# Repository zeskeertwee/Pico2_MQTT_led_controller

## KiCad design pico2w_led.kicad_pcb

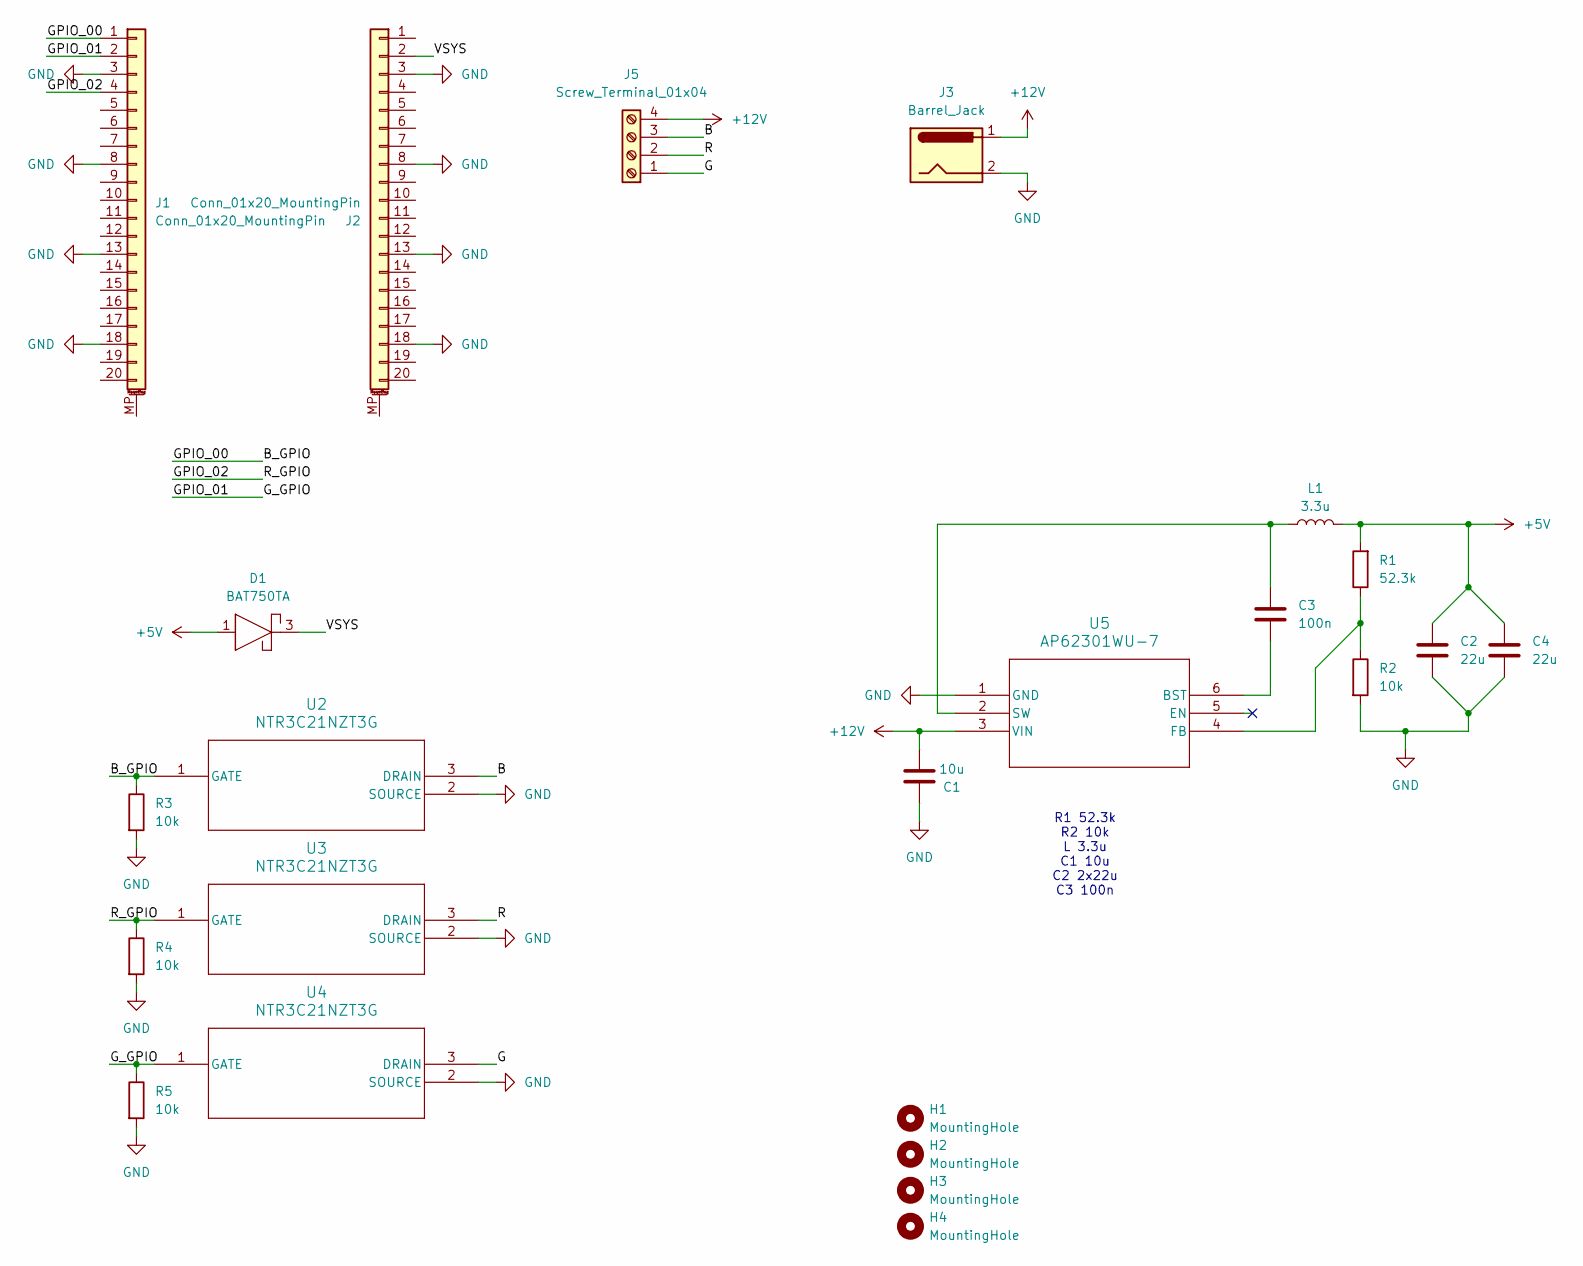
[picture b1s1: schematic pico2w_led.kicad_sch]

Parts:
C1: 10u; C_0805_2012Metric
C2, C4: 22u; C_1206_3216Metric
C3: 100n; C_0805_2012Metric
D1: BAT750TA; TSOT-23
H1, H2, H3, H4: MountingHole; MountingHole_2.2mm_M2
J1, J2: Conn_01x20_MountingPin; PinSocket_1x20_P2.54mm_Vertical
J3: Barrel_Jack; BarrelJack_CUI_PJ-063AH_Horizontal
J5: Screw_Terminal_01x04; TBD05-04-1-G-G
L1: 3.3u; IND_EPCOS_B82432T_EPC
R1: 52.3k; R_0805_2012Metric
R2, R3, R4, R5: 10k; R_1206_3216Metric
U2, U3, U4: NTR3C21NZT3G; SOT-23-3
U5: AP62301WU-7; TSOT26STANDARD_DIO

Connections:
+5V: C2.2, C4.2, D1.1, L1.2, R1.2
+12V: C1.1, J3.1, J5.4, U5.3 (VIN); also elsewhere on the board
/B: J5.3, U2.3 (DRAIN); also elsewhere on the board
/B_GPIO: J1.1, R3.1, U2.1 (GATE)
/G: J5.1, U4.3 (DRAIN); also elsewhere on the board
/GPIO_01: J1.2, R5.1, U4.1 (GATE)
/GPIO_02: J1.4, R4.1, U3.1 (GATE)
/R: J5.2, U3.3 (DRAIN); also elsewhere on the board
/VSYS: D1.3, J2.2
GND: C1.2, C2.1, C4.1, J1.3, J1.8, J1.13, J1.18, J2.3, J2.8, J2.13, J2.18, J3.2, R2.2, R3.2, R4.2, R5.2, U2.2 (SOURCE), U3.2 (SOURCE), U4.2 (SOURCE), U5.1 (GND)
unnamed: C3.2, U5.6 (BST)
unnamed: R1.1, R2.1, U5.4 (FB)
unnamed: C3.1, L1.1, U5.2 (SW)

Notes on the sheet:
R1 52.3k R2 10k L 3.3u C1 10u C2 2x22u C3 100n

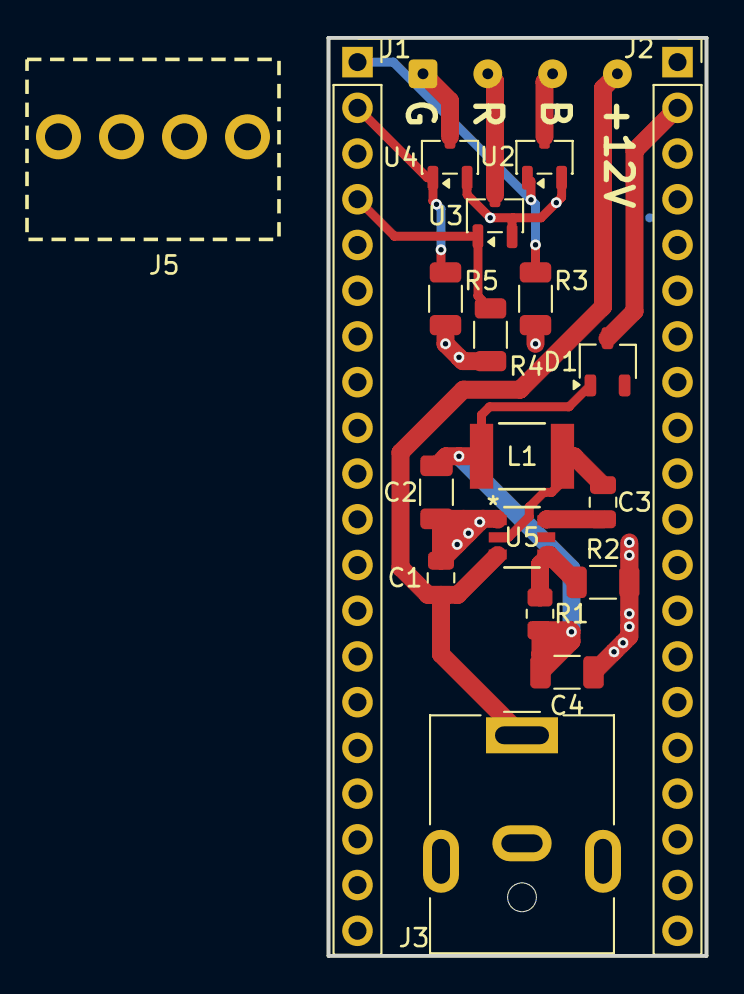
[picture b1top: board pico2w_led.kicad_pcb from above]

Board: 2 copper layers, 21.0 x 51.0 mm, 24 parts (1 on the bottom side), 13 nets.

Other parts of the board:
J4: Conn_01x04; SolderWire-0.1sqmm_1x04_P3.6mm_D0.4mm_OD1mm

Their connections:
+12V: J4.4; also elsewhere on the board
/B: J4.3; also elsewhere on the board
/G: J4.1; also elsewhere on the board
/R: J4.2; also elsewhere on the board

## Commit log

2026-01-04 Add pin header part numbers
2026-01-04 add bleed resistors
2026-01-05 Add screw terminal
